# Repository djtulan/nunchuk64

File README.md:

Nunchuk64 is a converter or adapter to connect a Wii Nunchuk or a Nindendo NES Classic Mini Controller
to a Commodore 64. The circuit converts two Nintendo Controllers into two Commodore 64 ones.
All types of the Commodore 64 inputs, which means digital and analog inputs, are available.

## Introduction Video
User [dukestah] from [Forum64](https://www.forum64.de) made a nice introduction video.
He gives a short introduction how the thing works in basic and demonstrates the functions while playing a game.

## Layout and PCB
The whole KiCad project is provided inside subfolder ["hardware"](./hardware).

Please feel free to order your own PCBs, Gerber files are here ["gerber"](./hardware/nunchuk64/gerber).

I would be pleased about a small donation: [PAYPAL.ME](https://www.paypal.me/RobertGrasboeck)

If somebody wants order a DIY kit, feel free to contact me: r o b e r t . g r a s b o e c k [at] g m a i l . c o m

## 3D Picture

## Supported and tested Hardware
Currently the following hardware is supported (see [Supported Controllers](./supported_controllers))

## Milestones
- ☑ Tested with a "Nindendo NES Classic Mini Controller" clone
- ☑ Tested with a "original Nindendo Nunchuk Controller"
- ☑ Tested with a "Nindendo Nunchuk Controller" clone
- ☑ Tested with different other NES/SNES Classic Mini clones

## Dependecies
- KiCad to work in schematic and layout (see [KiCad](http://kicad.org/))
- avr-gcc toolchain for compiling the firmware

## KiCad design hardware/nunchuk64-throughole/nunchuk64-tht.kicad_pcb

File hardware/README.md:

Hardware
==============
In this folder you can find all the needed parts to order the pcb.
The subfolder "nunchuk64" hold the KiCad project and Gerber files.

BOM
---
| Name           |Quantity|Value         |Footprint                     |
| ---------------|--------|--------------|------------------------------|
| U1             | 1      |AMS1117-3V3   |SOT-223                       |
| U2             | 1      |ATMEGA328P-AU |TQFP-32_7x7mm_Pitch0.8mm      |
| C1,C2          | 2      |22uF Tantalum |Tantalum_Case-A_EIA-3216-18   |
| C3,C4,C5       | 3      |100n          |0805                          |
| D1             | 1      |LED           |LED_1206                      |
| J1,J2          | 2      |DB9_Female    |DSUB-9 EdgeMount_Pitch 2.77mm |
| J3             | 1      |2x3 pin       |                              | 
| P1,P2          | 2      |CONN_WII      |Connector_Wii                 |
| Q1,Q2,Q3,Q4    | 4      |BSS138        |SOT-23                        |
| R9             | 1      |220           |0805                          |
| R4,R5,R6,R7,R10| 5      |10K           |0805                          |
| R1,R2,R3,R8    | 4      |2,2K          |0805                          |
| SW             | 1      |SW_Push       |Buttons Switch 6mm 13mm lenght|

The ready PCBs
--------------

PCB with parts
--------------

connected to C64:
--------------

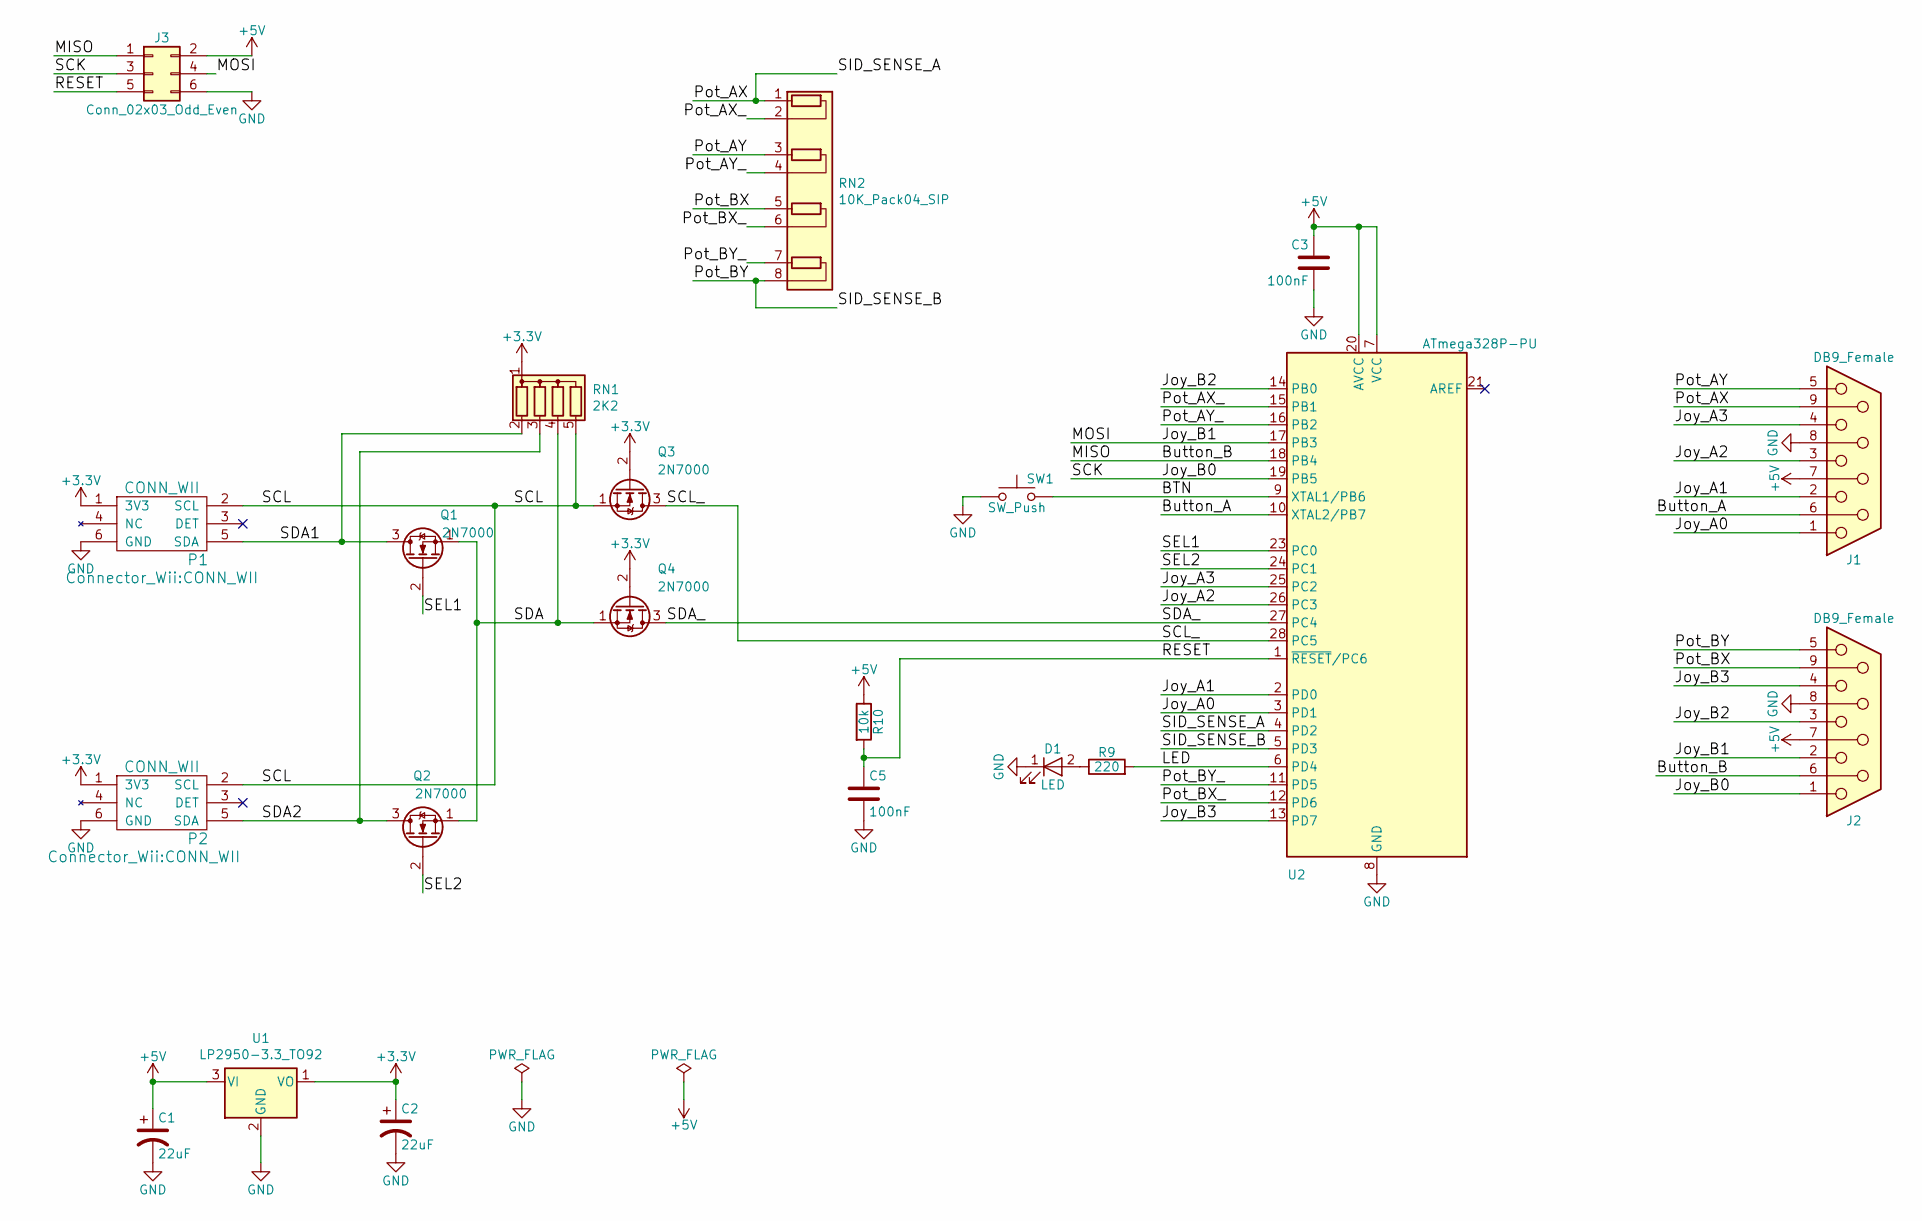
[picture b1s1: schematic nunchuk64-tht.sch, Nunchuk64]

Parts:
C1, C2: 22uF; CP_Radial_D5.0mm_P2.50mm
C3, C5: 100nF; C_Disc_D5.0mm_W2.5mm_P5.00mm
D1: LED; LED_D3.0mm
J1, J2: DB9_Female; DSUB-9_Female_EdgeMount_Pitch2.77mm
J3: Conn_02x03_Odd_Even; AVR-ISP-6-TH
P1, P2: CONN_WII
Q1, Q2, Q3, Q4: 2N7000; TO-92_Inline
R9: 220; R_Axial_DIN0207_L6.3mm_D2.5mm_P7.62mm_Horizontal
R10: 10k; R_Axial_DIN0207_L6.3mm_D2.5mm_P7.62mm_Horizontal
RN1: 2K2; R_Array_SIP5
RN2: 10K_Pack04_SIP; R_Array_SIP8
SW1: SW_Push; SW_PUSH_6mm_h13mm
U1: LP2950-3.3_TO92; TO-92_Inline_Wide
U2: ATmega328P-PU; DIP-28_W7.62mm

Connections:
+3V3: C2.1, P1.1 (3V3), P2.1 (3V3), Q3.2 (G), Q4.2 (G), RN1.1 (common), U1.1 (VO)
+5V: C1.1, C3.1, J1.7, J2.7, J3.2, R10.1, U1.3 (VI), U2.7 (VCC), U2.20 (AVCC)
/BTN: SW1.2, U2.9 (XTAL1/PB6)
/Button_A: J1.6, U2.10 (XTAL2/PB7)
/Button_B: J2.6, J3.1, U2.18 (PB4)
/Joy_A0: J1.1, U2.3 (PD1)
/Joy_A1: J1.2, U2.2 (PD0)
/Joy_A2: J1.3, U2.26 (PC3)
/Joy_A3: J1.4, U2.25 (PC2)
/Joy_B0: J2.1, J3.3, U2.19 (PB5)
/Joy_B1: J2.2, J3.4, U2.17 (PB3)
/Joy_B2: J2.3, U2.14 (PB0)
/Joy_B3: J2.4, U2.13 (PD7)
/LED: R9.2, U2.6 (PD4)
/Pot_AX: J1.9, RN2.1 (R1.1), U2.4 (PD2)
/Pot_AX_: RN2.2 (R1.2), U2.15 (PB1)
/Pot_AY: J1.5, RN2.3 (R2.1)
/Pot_AY_: RN2.4 (R2.2), U2.16 (PB2)
/Pot_BX: J2.9, RN2.5 (R3.1)
/Pot_BX_: RN2.6 (R3.2), U2.12 (PD6)
/Pot_BY: J2.5, RN2.8 (R4.2), U2.5 (PD3)
/Pot_BY_: RN2.7 (R4.1), U2.11 (PD5)
/RESET: C5.1, J3.5, R10.2, U2.1 (~RESET~/PC6)
/SCL: P1.2 (SCL), P2.2 (SCL), Q3.1 (S), RN1.5 (R4)
/SCL_: Q3.3 (D), U2.28 (PC5)
/SDA: Q1.1 (S), Q2.1 (S), Q4.1 (S), RN1.4 (R3)
/SDA1: P1.5 (SDA), Q1.3 (D), RN1.2 (R1)
/SDA2: P2.5 (SDA), Q2.3 (D), RN1.3 (R2)
/SDA_: Q4.3 (D), U2.27 (PC4)
/SEL1: Q1.2 (G), U2.23 (PC0)
/SEL2: Q2.2 (G), U2.24 (PC1)
GND: C1.2, C2.2, C3.2, C5.2, D1.1 (K), J1.8, J2.8, J3.6, P1.6 (GND), P2.6 (GND), SW1.1, U1.2 (GND), U2.8 (GND), U2.22 (GND)
unnamed: D1.2 (A), R9.1

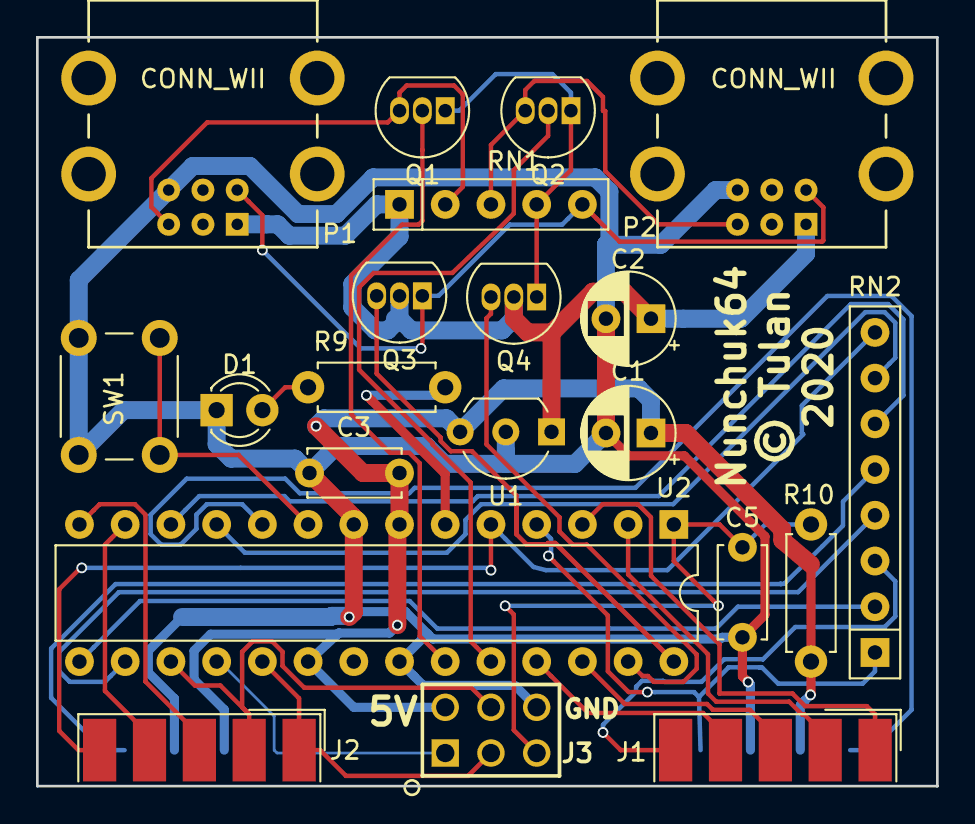
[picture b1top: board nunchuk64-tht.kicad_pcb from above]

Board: 2 copper layers, 50.0 x 41.6 mm, 21 parts (0 on the bottom side), 33 nets.

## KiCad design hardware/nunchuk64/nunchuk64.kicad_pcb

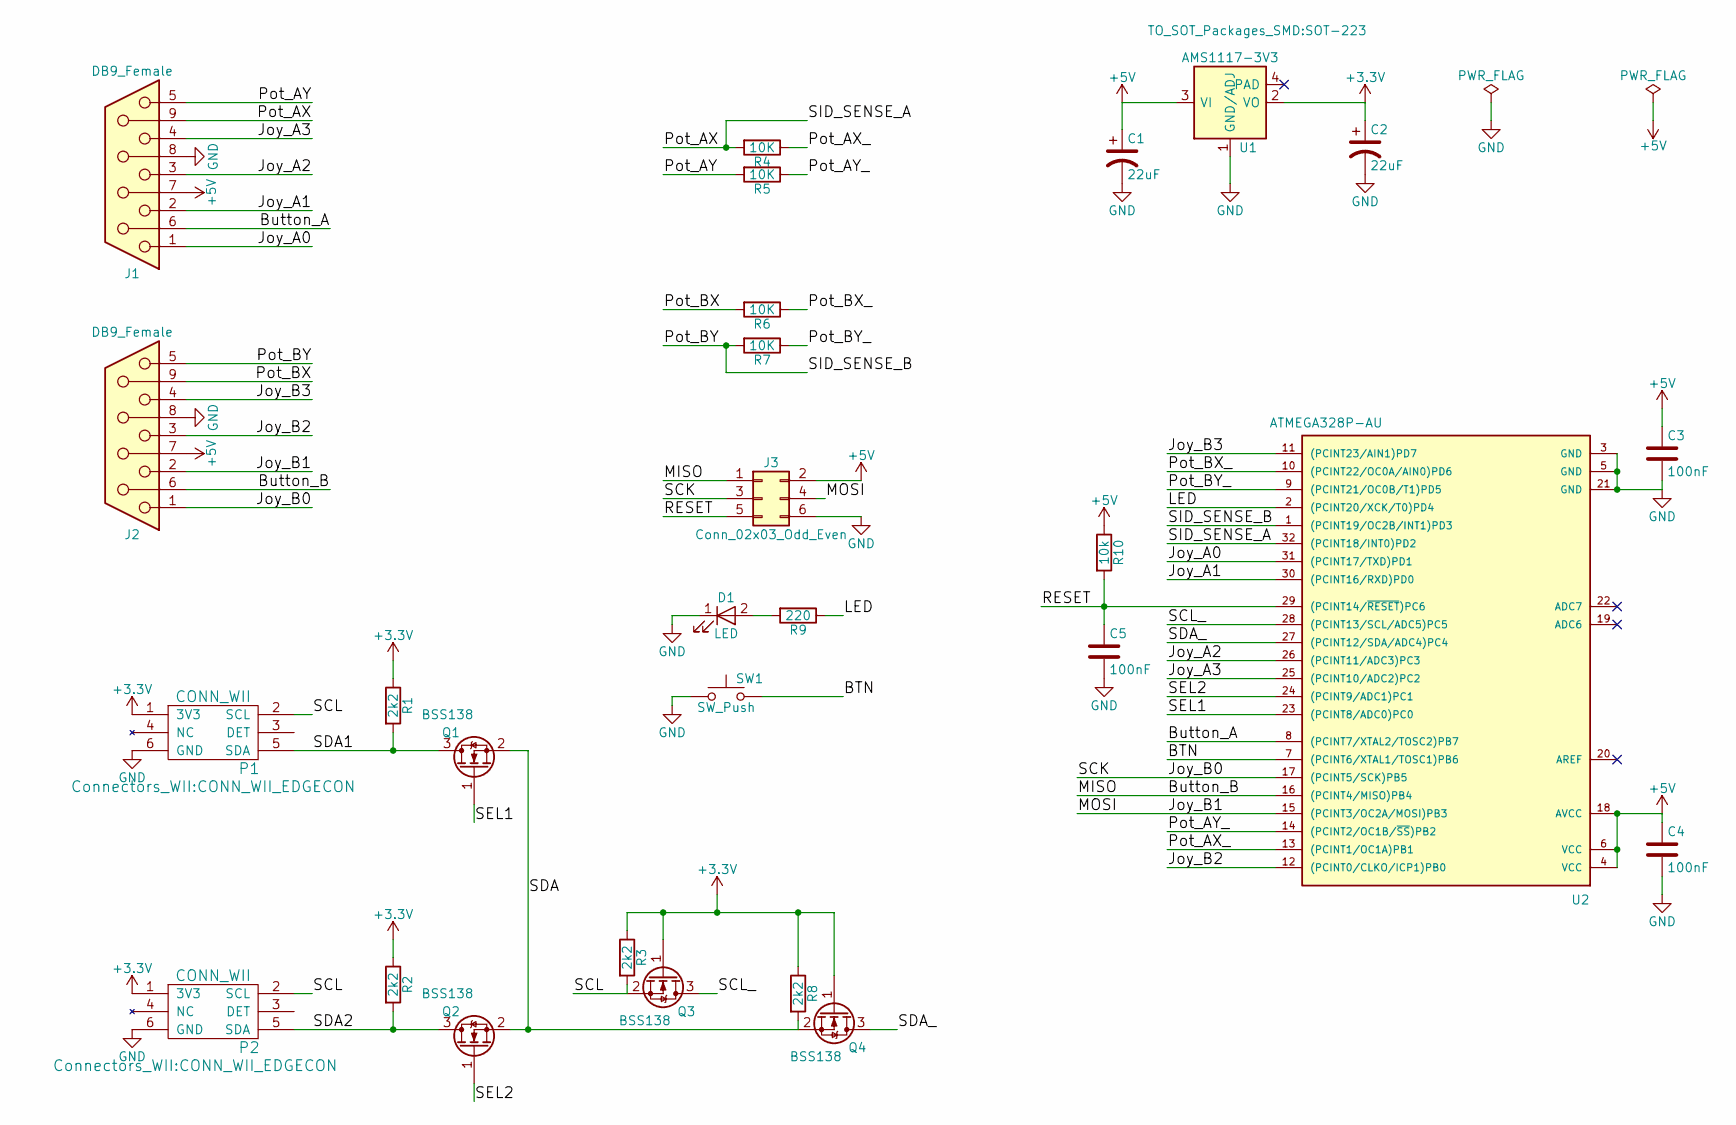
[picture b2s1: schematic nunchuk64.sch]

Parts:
C1, C2: 22uF; CP_Tantalum_Case-A_EIA-3216-18_Hand
C3, C4, C5: 100nF; C_0805_HandSoldering
D1: LED; LED_1206_HandSoldering
J1, J2: DB9_Female; DSUB-9_Female_EdgeMount_Pitch2.77mm
J3: Conn_02x03_Odd_Even; AVR-ISP-6-TH
P1, P2: CONN_WII; CONN_WII_EDGECON
Q1, Q2, Q3, Q4: BSS138; SOT-23_Handsoldering
R1, R2, R3, R8: 2k2; R_0805_HandSoldering
R4, R5, R6, R7: 10K; R_0805_HandSoldering
R9: 220; R_0805_HandSoldering
R10: 10k; R_0805_HandSoldering
SW1: SW_Push; SW_PUSH_6mm_h13mm
U1: AMS1117-3V3; SOT-223; MPN LM1117
U2: ATMEGA328P-AU; TQFP-32_7x7mm_Pitch0.8mm

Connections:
+3V3: C2.1, P1.1 (3V3), P2.1 (3V3), Q3.1 (G), Q4.1 (G), R1.1, R2.1, R3.1, R8.1, U1.2 (VO)
+5V: C1.1, C3.1, C4.1, J1.7, J2.7, J3.2, R10.1, U1.3 (VI), U2.4 (VCC), U2.6 (VCC), U2.18 (AVCC)
/BTN: SW1.2, U2.7 ((PCINT6/XTAL1/TOSC1)PB6)
/Button_A: J1.6, U2.8 ((PCINT7/XTAL2/TOSC2)PB7)
/Button_B: J2.6, J3.1, U2.16 ((PCINT4/MISO)PB4)
/Joy_A0: J1.1, U2.31 ((PCINT17/TXD)PD1)
/Joy_A1: J1.2, U2.30 ((PCINT16/RXD)PD0)
/Joy_A2: J1.3, U2.26 ((PCINT11/ADC3)PC3)
/Joy_A3: J1.4, U2.25 ((PCINT10/ADC2)PC2)
/Joy_B0: J2.1, J3.3, U2.17 ((PCINT5/SCK)PB5)
/Joy_B1: J2.2, J3.4, U2.15 ((PCINT3/OC2A/MOSI)PB3)
/Joy_B2: J2.3, U2.12 ((PCINT0/CLKO/ICP1)PB0)
/Joy_B3: J2.4, U2.11 ((PCINT23/AIN1)PD7)
/LED: R9.1, U2.2 ((PCINT20/XCK/T0)PD4)
/Pot_AX: J1.9, R4.2, U2.32 ((PCINT18/INT0)PD2)
/Pot_AX_: R4.1, U2.13 ((PCINT1/OC1A)PB1)
/Pot_AY: J1.5, R5.2
/Pot_AY_: R5.1, U2.14 ((PCINT2/OC1B/~SS~)PB2)
/Pot_BX: J2.9, R6.2
/Pot_BX_: R6.1, U2.10 ((PCINT22/OC0A/AIN0)PD6)
/Pot_BY: J2.5, R7.2, U2.1 ((PCINT19/OC2B/INT1)PD3)
/Pot_BY_: R7.1, U2.9 ((PCINT21/OC0B/T1)PD5)
/RESET: C5.1, J3.5, R10.2, U2.29 ((PCINT14/~RESET~)PC6)
/SCL: P1.2 (SCL), P2.2 (SCL), Q3.2 (S), R3.2
/SCL_: Q3.3 (D), U2.28 ((PCINT13/SCL/ADC5)PC5)
/SDA: Q1.2 (S), Q2.2 (S), Q4.2 (S), R8.2
/SDA1: P1.5 (SDA), Q1.3 (D), R1.2
/SDA2: P2.5 (SDA), Q2.3 (D), R2.2
/SDA_: Q4.3 (D), U2.27 ((PCINT12/SDA/ADC4)PC4)
/SEL1: Q1.1 (G), U2.23 ((PCINT8/ADC0)PC0)
/SEL2: Q2.1 (G), U2.24 ((PCINT9/ADC1)PC1)
GND: C1.2, C2.2, C3.2, C4.2, C5.2, D1.1 (K), J1.8, J2.8, J3.6, P1.6 (GND), P2.6 (GND), SW1.1, U1.1 (GND/ADJ), U2.3 (GND), U2.5 (GND), U2.21 (GND)
unnamed: D1.2 (A), R9.2

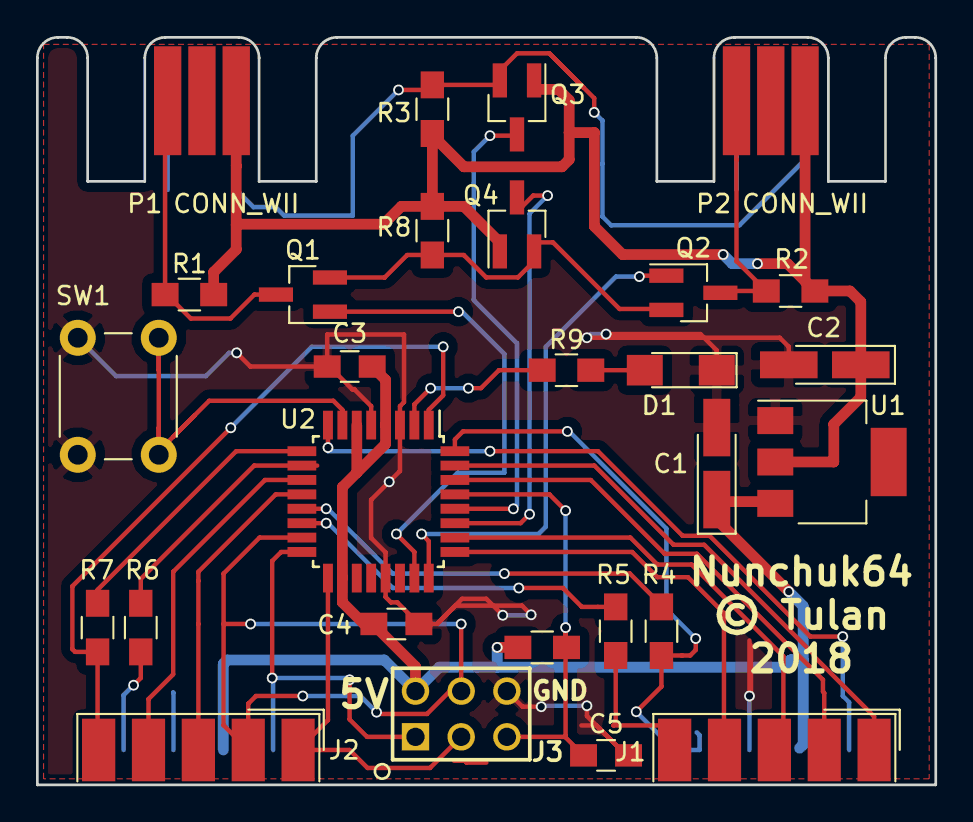
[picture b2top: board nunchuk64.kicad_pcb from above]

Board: 2 copper layers, 49.9 x 41.5 mm, 28 parts (0 on the bottom side), 33 nets.

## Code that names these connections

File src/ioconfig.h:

//=============================================================================
// *** Nunchuk64 ***
// Copyright (c) Robert Grasböck, All rights reserved.
//
// This program is free software: you can redistribute it and/or modify
// it under the terms of the GNU General Public License as published by
// the Free Software Foundation, either version 3 of the License, or
// (at your option) any later version.
//
// This program is distributed in the hope that it will be useful,
// but WITHOUT ANY WARRANTY; without even the implied warranty of
// MERCHANTABILITY or FITNESS FOR A PARTICULAR PURPOSE.  See the
// GNU General Public License for more details.
//
// You should have received a copy of the GNU General Public License
// along with this program.  If not, see <http://www.gnu.org/licenses/>.
//=============================================================================
/// @file   ioconfig.h
/// @author Robert Grasböck (robert.grasboeck@gmail.com)
/// @date   December, 2017
/// @brief  io pin configuration
//=============================================================================
#ifndef _IOCONFIG_H_
#define _IOCONFIG_H_

#include <avr/io.h>

#define BIT_GET(ADR,BIT)   ((ADR) & (_BV(BIT)))
#define BIT_SET(ADR,BIT)   ((ADR) |= (_BV(BIT)))
#define BIT_CLEAR(ADR,BIT) ((ADR) &= ~(_BV(BIT)))
#define BIT_FLIP(ADR,BIT)  ((ADR) ^= (_BV(BIT)))

// ========================================================
//  LED
// ========================================================

// led port, ddr and bit
#define PORT_LED           PORTD // PD4
#define DDR_LED             DDRD // PD4
#define BIT_LED                4 // PD4

// ========================================================
//  BUTTON
// ========================================================

// button port, ddr and bit
#define PIN_BUTTON          PINB // PB6
#define PORT_BUTTON        PORTB // PB6
#define DDR_BUTTON          DDRB // PB6
#define BIT_BUTTON             6 // PB6

// ========================================================
//  I2C Select
// ========================================================

// select1 port, ddr and bit
#define PORT_SEL1          PORTC // PC0
#define DDR_SEL1            DDRC // PC0
#define BIT_SEL1               0 // PC0

// select2 port, ddr and bit
#define PORT_SEL2          PORTC // PC1
#define DDR_SEL2            DDRC // PC1
#define BIT_SEL2               1 // PC1

// ========================================================
//  DIGITAL JOYSTICK OUTPUTS
// ========================================================

// io register for joystick outputs
#define PORT_JOY_A0        PORTD // PD1
#define PORT_JOY_A1        PORTD // PD0
#define PORT_JOY_A2        PORTC // PC3
#define PORT_JOY_A3        PORTC // PC2
#define PORT_BUTTON_A      PORTB // PB7
#define PORT_BUTTON2_A     PORTB // PB1
#define PORT_BUTTON3_A     PORTB // PB2 
#define PORT_JOY_B0        PORTB // PB5
#define PORT_JOY_B1        PORTB // PB3
#define PORT_JOY_B2        PORTB // PB0
#define PORT_JOY_B3        PORTD // PD7
#define PORT_BUTTON_B      PORTB // PB4
#define PORT_BUTTON2_B     PORTD // PD5
#define PORT_BUTTON3_B     PORTD // PD6


// ddr for joystick outputs
#define DDR_JOY_A0          DDRD // PD1
#define DDR_JOY_A1          DDRD // PD0
#define DDR_JOY_A2          DDRC // PC3
#define DDR_JOY_A3          DDRC // PC2
#define DDR_BUTTON_A        DDRB // PB7
#define DDR_BUTTON2_A       DDRB // PB1
#define DDR_BUTTON3_A       DDRB // PB2
#define DDR_JOY_B0          DDRB // PB5
#define DDR_JOY_B1          DDRB // PB3
#define DDR_JOY_B2          DDRB // PB0
#define DDR_JOY_B3          DDRD // PD7
#define DDR_BUTTON_B        DDRB // PB4
#define DDR_BUTTON2_B       DDRD // PD6
#define DDR_BUTTON3_B       DDRD // PD5

// bits for joystick outputs
#define BIT_JOY_A0             1 // PD1
#define BIT_JOY_A1             0 // PD0
#define BIT_JOY_A2             3 // PC3
#define BIT_JOY_A3             2 // PC2
#define BIT_BUTTON_A           7 // PB7
#define BIT_BUTTON2_A          1 // PB1
#define BIT_BUTTON3_A          2 // PB2
#define BIT_JOY_B0             5 // PB5
#define BIT_JOY_B1             3 // PB3
#define BIT_JOY_B2             0 // PB0
#define BIT_JOY_B3             7 // PD7
#define BIT_BUTTON_B           4 // PB4
#define BIT_BUTTON2_B          6 // PD6
#define BIT_BUTTON3_B          5 // PD5

// ========================================================
//  PADDLE INPUTS & OUTPUTS
// ========================================================

// io register for paddle inputs / outputs
#define PORT_SENSE_A       PORTD // PD2
#define PORT_PADDLE_A_X    PORTB // PB1
#define PORT_PADDLE_A_Y    PORTB // PB2

#define PORT_SENSE_B       PORTD // PD3
#define PORT_PADDLE_B_Y    PORTD // PD5
#define PORT_PADDLE_B_X    PORTD // PD6

// ddr for paddle inputs / outputs
#define DDR_SENSE_A         DDRD // PD2
#define DDR_PADDLE_A_X      DDRB // PB1
#define DDR_PADDLE_A_Y      DDRB // PB2

#define DDR_SENSE_B         DDRD // PD3
#define DDR_PADDLE_B_X      DDRD // PD6
#define DDR_PADDLE_B_Y      DDRD // PD5

// bits for paddle sense
#define BIT_SENSE_A            2 // PD2
#define BIT_PADDLE_A_X         1 // PB1
#define BIT_PADDLE_A_Y         2 // PB2

#define BIT_SENSE_B            3 // PD3
#define BIT_PADDLE_B_X         6 // PD6
#define BIT_PADDLE_B_Y         5 // PD5

#endif

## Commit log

2017-12-30 added Makefile and nunchuck64.c
2017-12-30 added some files
2017-12-30 added gerber files
2017-12-30 added README.md
2017-12-30 changed Readme
2017-12-31 changed Readme, added work in progress
2017-12-31 added c-file header
2017-12-31 added c code
2018-01-06 added c code & pdf
2018-01-07 updated code
2018-01-07 fixed lock bits
2018-01-07 fixed reformat bug
2018-01-07 renamed file
2018-01-07 added new files
2018-01-08 first part of analog input
2018-01-09 analog paddle changes
2018-01-15 added driver struct, added some helper marcos
2018-01-16 changed driver base, added nunchuk driver, added detection
2018-01-21 added doxy docu
2018-01-21 added button, led and selector modules
2018-01-21 code cleanup, docu
2018-01-22 added list to readme
2018-01-23 added driver wii classic
2018-02-01 added ID of NES classic mini chinese clone, improved driver
2018-02-01 added missing kicad libraries
2018-02-02 bugfixed nunchuk init, cleanup, nunchuck accelerometer
2018-02-02 fixed Make fuses
2018-02-10 added more led states, changed paddle code
2018-02-10 support for SNES Clone, added SPACE on both START controller
2018-02-12 support for WII Classic Clone, same id NES/SNES Mini clone
2018-02-13 added new folder supported controllers
2018-02-13 changed filename
2018-02-13 added controller pictures
2018-02-14 fixed controller identification and encryption
2018-02-14 faster joystick code
2018-02-14 led blink code with timer
2018-02-14 removed led_poll call in mainloop
2018-02-14 added new controller picture
2018-02-14 added controller picture description
2018-02-14 added controller description
2018-02-14 fixed controller description
2018-02-22 made i2c bus faster, added DEFINES for single controller config
2018-02-26 fixed problems with original nunchuk
2018-02-27 moved source to ./src
2018-02-28 added cosmetic change in layout
2018-02-28 changed readme, added YT link
2018-03-01 added timer files
2018-03-01 autofire
2018-03-01 added watchdog, added autofire
2018-03-01 changed watchdog
2018-03-01 changed some fire to autofire
2018-03-04 changed layout a bit
2018-03-04 new gerber files
2018-03-05 update schematic.pdf and 3d pic
2018-03-09 changed doxy docu
2018-03-09 changed led behaviour a bit
2018-03-09 Possibility to unplug and reconnect the controller. Single controller operation.
2018-03-10 reset joystick state, after disconnect, added old timings, nunchuk more sensitive
2018-03-10 readme update
2018-03-11 added analog states, changed paddle code, renamed selector functions
2018-03-11 changed paddle code
2018-03-11 removed delays
2018-03-11 fixed paddle
2018-03-12 removed F3 mode, switch ports now with longer button press
2018-03-13 added new enum ON/OFF, added joystick bits, added items to ioconfig
2018-03-13 update joystick and paddle mode
2018-03-18 update supported_controllers
2018-03-18 added led feedback for long press joystick switch
2018-03-18 update readme, removed work in progress
2018-03-19 added logo
2018-05-09 added assembly_instruction
2018-05-14 added assembly_instruction english, changed german
2018-05-15 commented nes classic driver code
2018-05-15 support for 8bitdo
2018-05-15 added part_placement.png
2018-06-17 updated supported_controllers/README.md
2018-06-23 Created fingers inside Connectors-Wii:CONN_WII for those hard to get connectors
2018-06-23 gerbers
2018-06-23 gerber files
2018-06-23 3D rendering
2018-06-25 Removed holes. Widen edge connector.
    allpcb didn't approve halfplated holes at the same price.
2018-06-27 rounded corners. wii_conn_edge replaces old conn
2018-06-29 Tidied up references on silk screen.
2018-07-06 fix: accidentally rotated a net. island gnd fill
2018-07-06 DRC OK
2018-07-17 Support for new Controller W60N107
2018-07-18 added support for 8bitdo RT und LT buttons
2018-07-18 changed wdt to 1sec
2018-12-19 Update README.md
    added BOM
2019-04-10 convert Makefile to ascii
2019-05-06 added cases/README.md
2019-05-06 removed id from supported controllres
2019-05-06 changed cases/README.md
2020-11-12 throughole version
2021-03-08 show size of the build after make
2021-03-08 nunchuk64-throughole version. bom with mouser parts.
2021-03-08 refreshed gerber files
2021-11-08 Update README.md
    https://forum.kicad.info/t/warning-avoid-all-links-to-kicad-pcb-org-use-kicad-org/31521
2022-05-26 fixed problem with traces shortcircuiting
2022-05-26 removed gerber.zip. Double-documentation == problems.

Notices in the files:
hardware/nunchuk64-throughole/nunchuk64-tht.kicad_pcb:
© Tulan
